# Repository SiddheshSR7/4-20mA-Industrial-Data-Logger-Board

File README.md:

**Project Overview: 4-20mA Industrial IoT Data Logger**

The 4-20mA Industrial IoT Data Logger is a high-precision data acquisition system designed for industrial automation, remote monitoring, and predictive maintenance applications. Engineered with robust hardware and intelligent software, this 4-layer PCB is developed using KiCad and features advanced communication protocols, real-time data logging, and IoT connectivity. This system ensures accurate monitoring of industrial processes, enabling seamless data exchange and control in demanding environments.

### **Hardware Specifications:**
- **Microcontroller:** ESP32-WROOM-S3 SoC with dual-core Xtensa LX7 processor, integrated Wi-Fi & Bluetooth connectivity, and low-power operation.
- **USB-UART Interface:** CP2102N IC enabling high-speed USB-to-serial communication for seamless programming and debugging.
- **Analog Input:** 4-channel 4-20mA analog input with high-precision ADC for industrial sensor interfacing and real-time data acquisition.
- **Relay Output:** 2-channel 24VDC fast-switching relay outputs designed for industrial control applications, supporting up to 3A load per channel.
- **Communication Interfaces:**
  - **RS232 (Full-Duplex):** Supports legacy industrial communication standards for serial device interfacing.
  - **RS485 (Half-Duplex):** Enables reliable long-distance communication in noisy industrial environments.
- **Data Storage:** SD card interface supporting high-capacity storage for logging and offline data retrieval.
- **Programming & Debugging:**
  - USB B-type connector for easy programming and firmware updates.
  - Dedicated UART debug port for real-time monitoring, diagnostics, and firmware development.
- **Power Specifications:**
  - Operating voltage: 24V DC.
  - Maximum current rating: 3A.
  - Efficient power management ensuring stable performance in industrial environments.

### **Software Features:**
- **IoT Dashboard Integration:** Secure cloud-based monitoring and control via an interactive web-based dashboard.
- **Over-the-Air (OTA) Updates:** Supports remote firmware upgrades, reducing downtime and maintenance efforts.
- **Configurable I/O:** User-defined configuration for analog input scaling and relay output control through an intuitive software interface.
- **MQTT Protocol:** Enables encrypted and reliable cloud communication, facilitating seamless data transmission for industrial automation.
- **Data Logging & Analytics:**
  - Real-time and historical data storage for trend analysis and predictive maintenance.
  - Secure SD card-based local logging for offline diagnostics.
- **Multi-Protocol Support:** Compatible with Modbus RTU, MQTT, and HTTP APIs for enhanced industrial IoT integration.

### **Applications:**
- Industrial process monitoring and control.
- Remote asset tracking and condition monitoring.
- SCADA system integration.
- Energy and utility monitoring.
- Predictive maintenance and fault detection.

The 4-20mA Industrial IoT Data Logger is a powerful solution for industrial automation, offering real-time data acquisition, secure cloud connectivity, and seamless integration into existing systems. Its combination of rugged hardware and intelligent software makes it an ideal choice for modern industrial applications requiring high accuracy, reliability, and efficiency.

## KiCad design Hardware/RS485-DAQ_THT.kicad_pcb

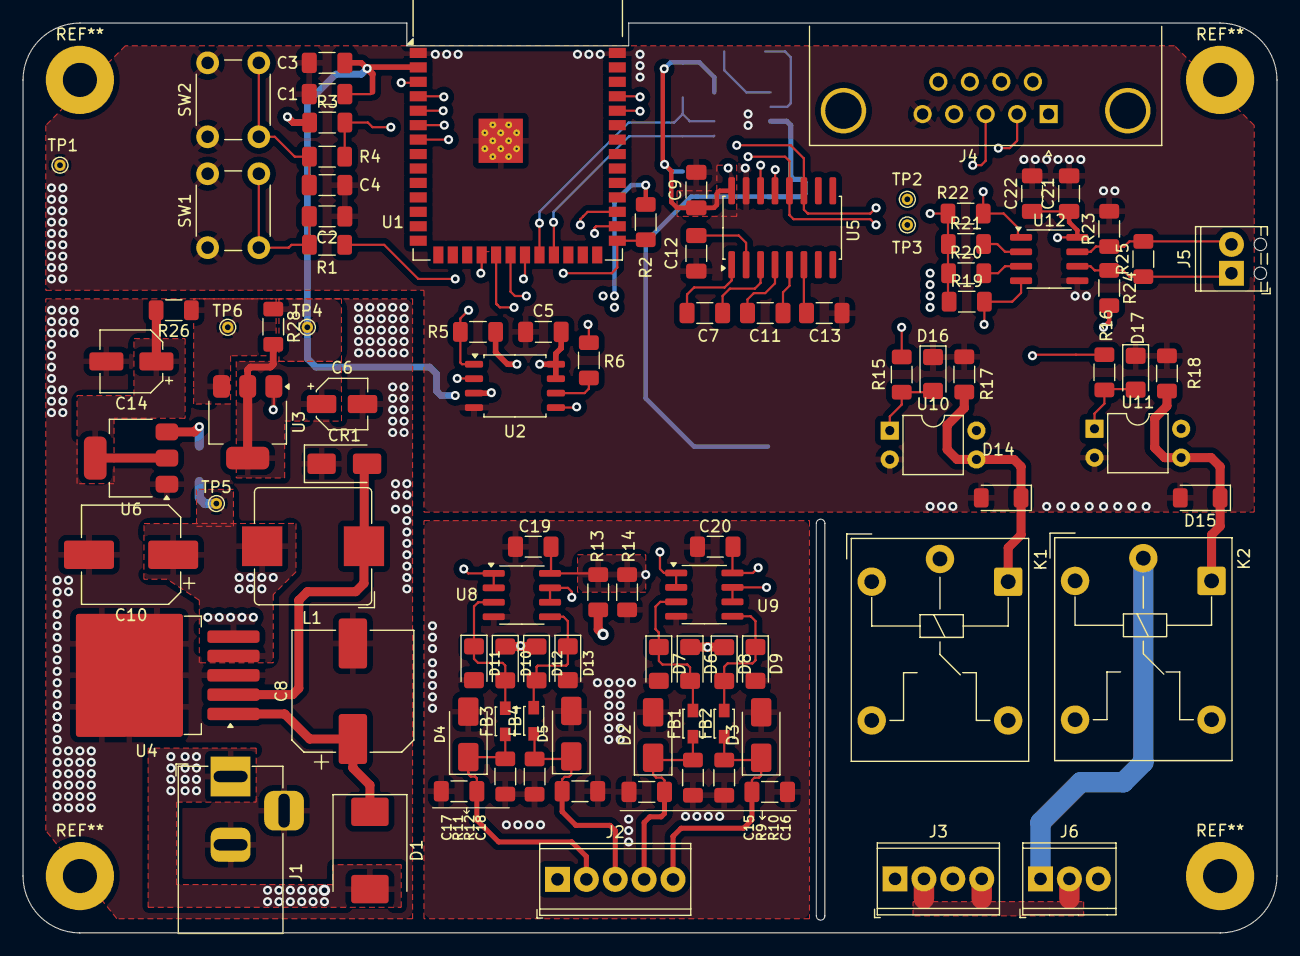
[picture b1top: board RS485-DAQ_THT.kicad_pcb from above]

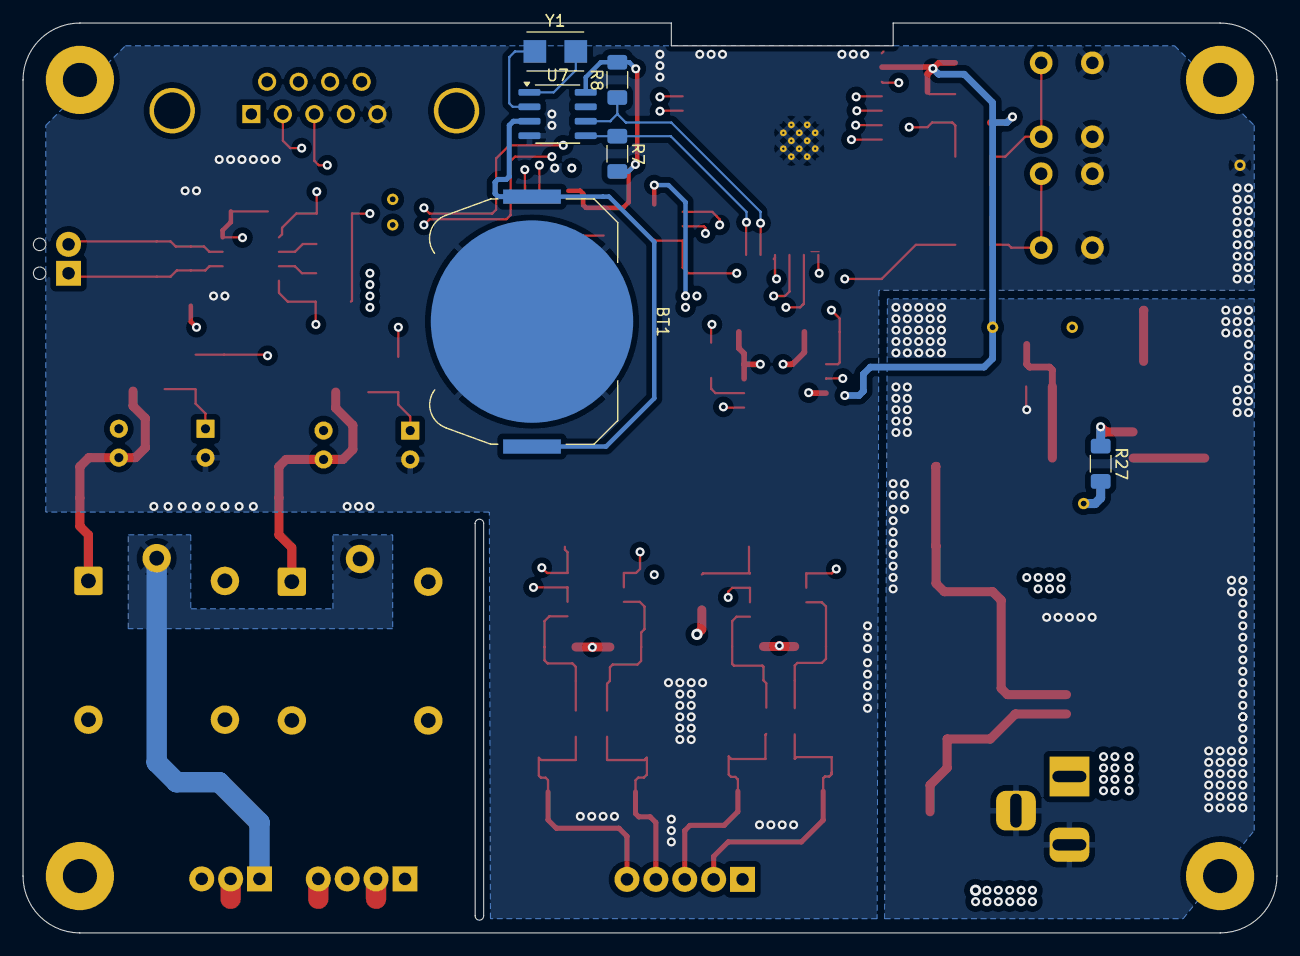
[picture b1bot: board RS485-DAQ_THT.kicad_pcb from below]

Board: 4 copper layers, 110.2 x 80.0 mm, 103 parts (6 on the bottom side), 61 nets.

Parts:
BT1: Battery_Cell; BatteryHolder_Keystone_3034_1x20mm
C1: 100uF/6.3V; C_1206_3216Metric_Pad1.33x1.80mm_HandSolder
C2, C4: 1nF/50V; C_1206_3216Metric_Pad1.33x1.80mm_HandSolder
C3: 1uF/10V; C_1206_3216Metric_Pad1.33x1.80mm_HandSolder
C5, C7, C9, C11, C12, C13, C21: 1uF; C_1206_3216Metric_Pad1.33x1.80mm_HandSolder
C6: 10uF/25V; CP_Elec_4x5.3
C8: 470uF 35V; CP_Elec_10x10.5
C10: 100uF 16V; CP_Elec_8x10.5
C14: 100uF 10V; CP_Elec_5x5.4
C15, C16, C17, C18: 1nF; C_1206_3216Metric_Pad1.33x1.80mm_HandSolder
C19, C20: 0.1uF; C_1206_3216Metric_Pad1.33x1.80mm_HandSolder
C22: 10uF; C_1206_3216Metric_Pad1.33x1.80mm_HandSolder
CR1: M7; D_SMA
D1: S3D; D_SMC
D2, D3, D4, D5: SMAJ18A; D_SMA
D6, D7, D8, D9, D10, D11, D12, D13: 1N5819; D_1206_3216Metric_Pad1.42x1.75mm_HandSolder
D14, D15: D_Zener; D_MiniMELF
D16, D17: LED; LED_1206_3216Metric_Pad1.42x1.75mm_HandSolder
FB1, FB2, FB3, FB4: FerriteBead; L_Walsin_WLFM201209x
J1: 24V Input; BarrelJack_Horizontal
J2: Analog Input; TerminalBlock_Phoenix_MPT-0,5-5-2.54_1x05_P2.54mm_Horizontal
J3: 2_Ch. AC Devices; TerminalBlock_Phoenix_MPT-0,5-4-2.54_1x04_P2.54mm_Horizontal
J4: DB9; DSUB-9_Male_Horizontal_P2.77x2.84mm_EdgePinOffset4.94mm_Hou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
J5: RS485; TerminalBlock_Phoenix_MPT-0,5-2-2.54_1x02_P2.54mm_Horizontal
J6: AC Input; TerminalBlock_Phoenix_MPT-0,5-3-2.54_1x03_P2.54mm_Horizontal
K1, K2: Relay_SPDT; Relay_SPDT_Hongfa_HF3F-L-xx-1ZL1T
L1: 68uH; L_Bourns_SRP1038C_10.0x10.0mm
R1, R4: 470R; R_1206_3216Metric_Pad1.30x1.75mm_HandSolder
R2: 5K; R_1206_3216Metric_Pad1.30x1.75mm_HandSolder
R3: 12K; R_1206_3216Metric_Pad1.30x1.75mm_HandSolder
R5: 10K; R_1206_3216Metric_Pad1.30x1.75mm_HandSolder
R6: 22R; R_1206_3216Metric_Pad1.30x1.75mm_HandSolder
R7, R8, R19, R20, R21, R22: 10k; R_1206_3216Metric_Pad1.30x1.75mm_HandSolder
R9, R10, R11, R12: 250R; R_1206_3216Metric_Pad1.30x1.75mm_HandSolder
R13, R15, R16: 330; R_1206_3216Metric_Pad1.30x1.75mm_HandSolder
R14: 300; R_1206_3216Metric_Pad1.30x1.75mm_HandSolder
R17, R18: 4.7K; R_1206_3216Metric_Pad1.30x1.75mm_HandSolder
R23, R24: 20k; R_1206_3216Metric_Pad1.30x1.75mm_HandSolder
R25: 120; R_1206_3216Metric_Pad1.30x1.75mm_HandSolder
R26, R27, R28: 0E; R_1206_3216Metric_Pad1.30x1.75mm_HandSolder
SW1, SW2: SW_Push; SW_PUSH_6mm_H5mm
TP1: GND; TestPoint_THTPad_D1.0mm_Drill0.5mm
TP2: TX_TP; TestPoint_THTPad_D1.0mm_Drill0.5mm
TP3: RX_TP; TestPoint_THTPad_D1.0mm_Drill0.5mm
TP4: +3.3V_TP; TestPoint_THTPad_D1.0mm_Drill0.5mm
TP5: +12V_TP; TestPoint_THTPad_D1.0mm_Drill0.5mm
TP6: +5V_TP; TestPoint_THTPad_D1.0mm_Drill0.5mm
U1: ESP32-S3-WROOM-1
U2: w25q64jvssiq; SOIC-8_5.23x5.23mm_P1.27mm
U3: AMS1117-3.3; SOT-223-3_TabPin2
U4: LM2596S-12; TO-263-5_TabPin3
U5: MAX232; SOIC-16W_5.3x10.2mm_P1.27mm
U6: AMS1117-5.0; SOT-223-3_TabPin2
U7: DS1307ZN+; SOIC-8_3.9x4.9mm_P1.27mm
U8, U9: LM358; SOIC-8_3.9x4.9mm_P1.27mm
U10, U11: PC817; DIP-4_W7.62mm
U12: MAX485E; SOIC-8_3.9x4.9mm_P1.27mm
Y1: 32.768KHz; Crystal_SMD_Qantek_QC5CB-2Pin_5x3.2mm

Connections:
5Vout: C9.1, C21.1, C22.1, R7.2, R8.2, R19.1, R20.1, R21.1, R22.1, R24.2, R26.1, TP6.1, U3.3 (VI), U5.16 (VCC), U7.8 (VCC), U12.8 (VCC)
24Vin: D1.A, J1.1, J2.1, U10.4, U11.4
/DAQ-1/+6.26V: C19.1, C20.1, R13.2, R14.1, U8.8 (V+), U9.8 (V+)
/DAQ-1/+12Vout: C10.1, D6.1 (K), D8.1 (K), D10.1 (K), D12.1 (K), L1.2, R13.1, R27.2, TP5.1, U4.4 (FB)
/DAQ-1/A1: C17.1, D4.1 (A1), FB3.1, J2.2, R11.1
/DAQ-1/A2: C18.1, D5.1 (A1), FB4.1, J2.3, R12.1
/DAQ-1/A3: C15.1, D2.1 (A1), FB1.1, J2.4, R9.1
/DAQ-1/A4: C16.1, D3.1 (A1), FB2.1, J2.5, R10.1
/DAQ-1/DAQ-2/DE: R20.2, U12.3 (DE)
/DAQ-1/DAQ-2/RE: R21.2, U12.2 (~RE)
/DAQ-1/DAQ-2/R_out1: D14.1 (K), K1.A1, R17.1, U10.3
/DAQ-1/DAQ-2/R_out2: D15.1 (K), K2.A1, R18.1, U11.3
/DAQ-1/RX_DB9: J4.2, U5.14 (T1OUT)
/DAQ-1/TX_DB9: J4.3, U5.13 (R1IN)
/EN: R3.2, R4.2, U1.3 (EN)
/IO0: R1.2, R2.1, U1.27 (IO0)
A: J5.1, R24.1, R25.1, U12.6 (A)
A1_out: U1.4 (IO4), U8.1, U8.2 (-)
A2_out: U1.5 (IO5), U8.6 (-), U8.7
A3_out: U1.6 (IO6), U9.1, U9.2 (-)
A4_out: U1.7 (IO7), U9.6 (-), U9.7
B: J5.2, R23.1, R25.2, U12.7 (B)
CLK: R6.2, U1.20 (IO12)
CS: R5.2, U1.18 (IO10), U2.1 (CS)
GND: BT1.2 (-), C1.2, C2.1, C3.2, C4.1, C5.1, C6.2, C8.2, C9.2, C10.2, C12.2, C13.2, C14.2, C15.2, C16.2, C17.2, C18.2, C19.2, C20.2, C21.2, C22.2, CR1.1, D2.2 (A2), D3.2 (A2), D4.2 (A2), D5.2 (A2), D7.2 (A), D9.2 (A), D11.2 (A), D13.2 (A), D14.2 (A), D15.2 (A), D16.1 (K), D17.1 (K), J1.2, J1.3, J4.5, K1.A2, K2.A2, R9.2, R10.2, R11.2, R12.2, R14.2, R17.2, R18.2, R23.2, SW1.1, SW2.1, TP1.1, U1.1 (GND), U1.40 (GND), U1.41 (GND), U2.4 (GND), U3.1 (GND), U4.3 (GND), U4.5 (~ON/OFF), U5.15 (GND), U6.1 (GND), U7.4 (GND), U8.4 (V-), U9.4 (V-), U10.2, U11.2, U12.5 (GND)
L: J6.1, K1.11, K2.11
MISO: U1.21 (IO13), U2.2 (DO(IO1))
MOSI: U1.19 (IO11), U2.5 (DI(IO0))
N: J3.2, J3.4, J6.2
NO1: J3.1, K1.14
NO2: J3.3, K2.14
unnamed: BT1.1 (+), U7.3 (VBAT)
unnamed: C2.2, R1.1, SW1.2
unnamed: C4.2, R4.1, SW2.2
unnamed: D6.2 (A), D7.1 (K), FB1.2, U9.3 (+)
unnamed: D8.2 (A), D9.1 (K), FB2.2, U9.5 (+)
unnamed: D10.2 (A), D11.1 (K), FB3.2, U8.3 (+)
unnamed: D12.2 (A), D13.1 (K), FB4.2, U8.5 (+)
unnamed: D16.2 (A), R15.2, U10.1
unnamed: D17.2 (A), R16.2, U11.1
unnamed: R6.1, U2.6 (CLK)
unnamed: C6.1, R28.2, U3.2 (VO)
unnamed: CR1.2, L1.1, U4.2 (OUT)
unnamed: C8.1, D1.C, U4.1 (VIN)
unnamed: C7.1, U5.1 (C1+)
unnamed: C7.2, U5.3 (C1-)
unnamed: C11.1, U5.4 (C2+)
unnamed: C11.2, U5.5 (C2-)
unnamed: C12.1, U5.2 (VS+)
unnamed: C13.1, U5.6 (VS-)
unnamed: R27.1, U6.3 (VI)
unnamed: C14.1, R26.2, U6.2 (VO)
unnamed: U7.1 (X1), Y1.2
unnamed: U7.2 (X2), Y1.1
RL_1: R15.1, U1.28 (IO35)
RL_2: R16.1, U1.29 (IO36)
RXD0: R19.2, TP3.1, U1.36 (RXD0), U5.12 (R1OUT), U12.4 (DI)
SCL: R8.1, U1.22 (IO14), U7.6 (SCL)
SDA: R7.1, U1.23 (IO21), U7.5 (SDA)
TXD0: R22.2, TP2.1, U1.37 (TXD0), U5.11 (T1IN), U12.1 (RO)
VDD: C1.1, C3.1, C5.2, R2.2, R3.1, R5.1, R28.1, TP4.1, U1.2 (3V3), U2.3 (WP(IO2)), U2.7 (HOLD/RES(IO3)), U2.8 (VCC)

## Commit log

2025-04-03 Hardware files structured
2025-04-03 Removed hardware project cache files
